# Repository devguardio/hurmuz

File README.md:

# Hürmüz - an rpi cm4 server board

Hürmüz is a devguard slice server board using the raspberry pi compute module 4 as CPU.

Ethernet is bundled via a KSZ9477 ethernet switch, where each CPU gets its own VLAN.
For recovery and management, USB is connected via an usb switch to an additional managment CPU.

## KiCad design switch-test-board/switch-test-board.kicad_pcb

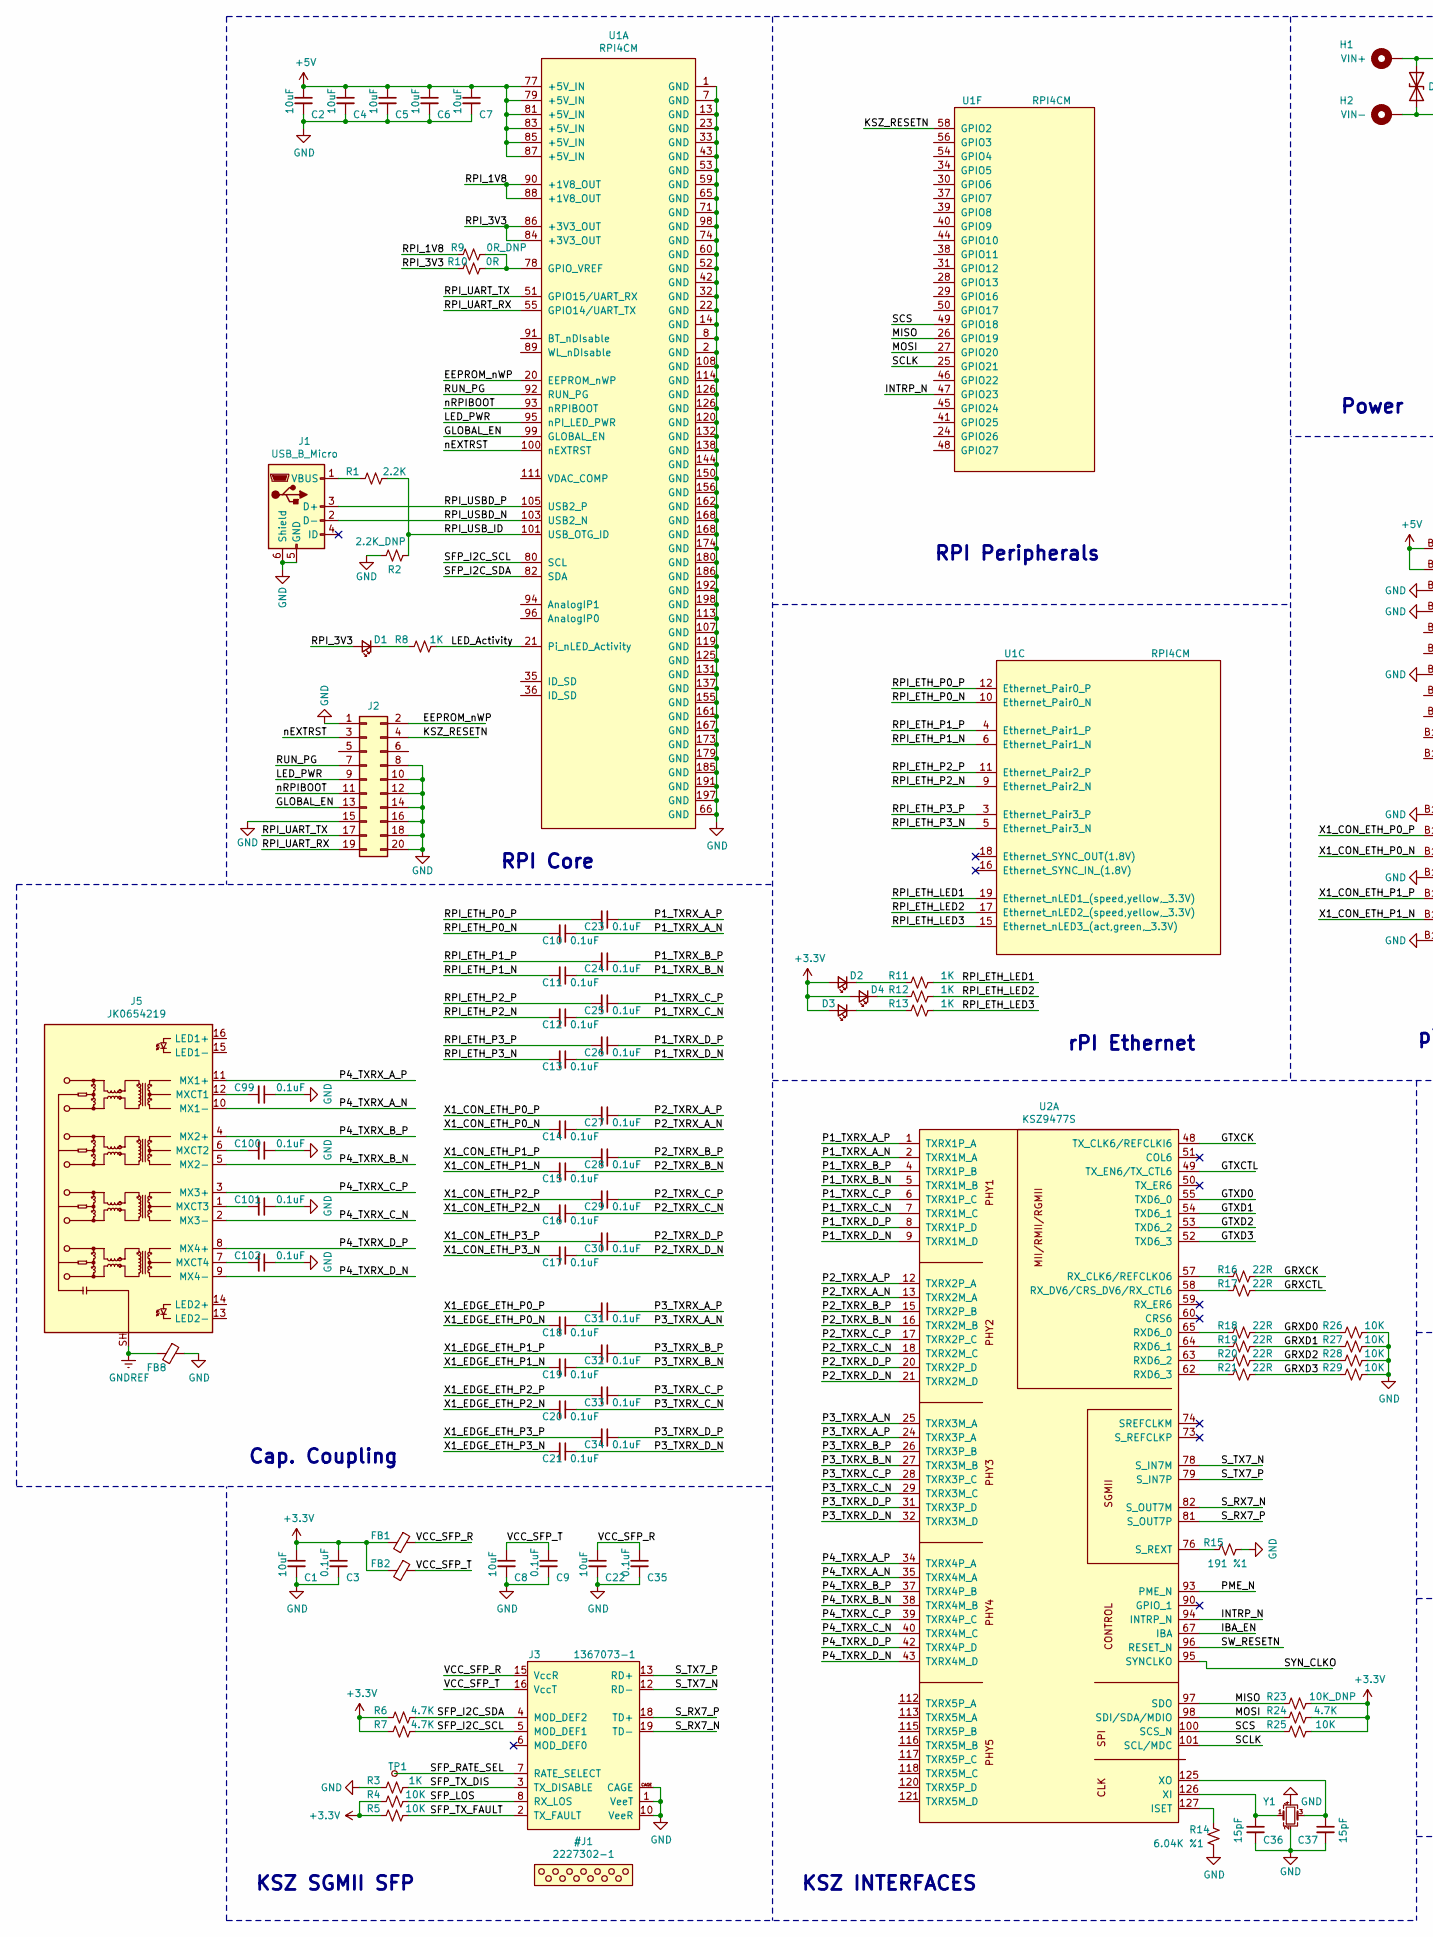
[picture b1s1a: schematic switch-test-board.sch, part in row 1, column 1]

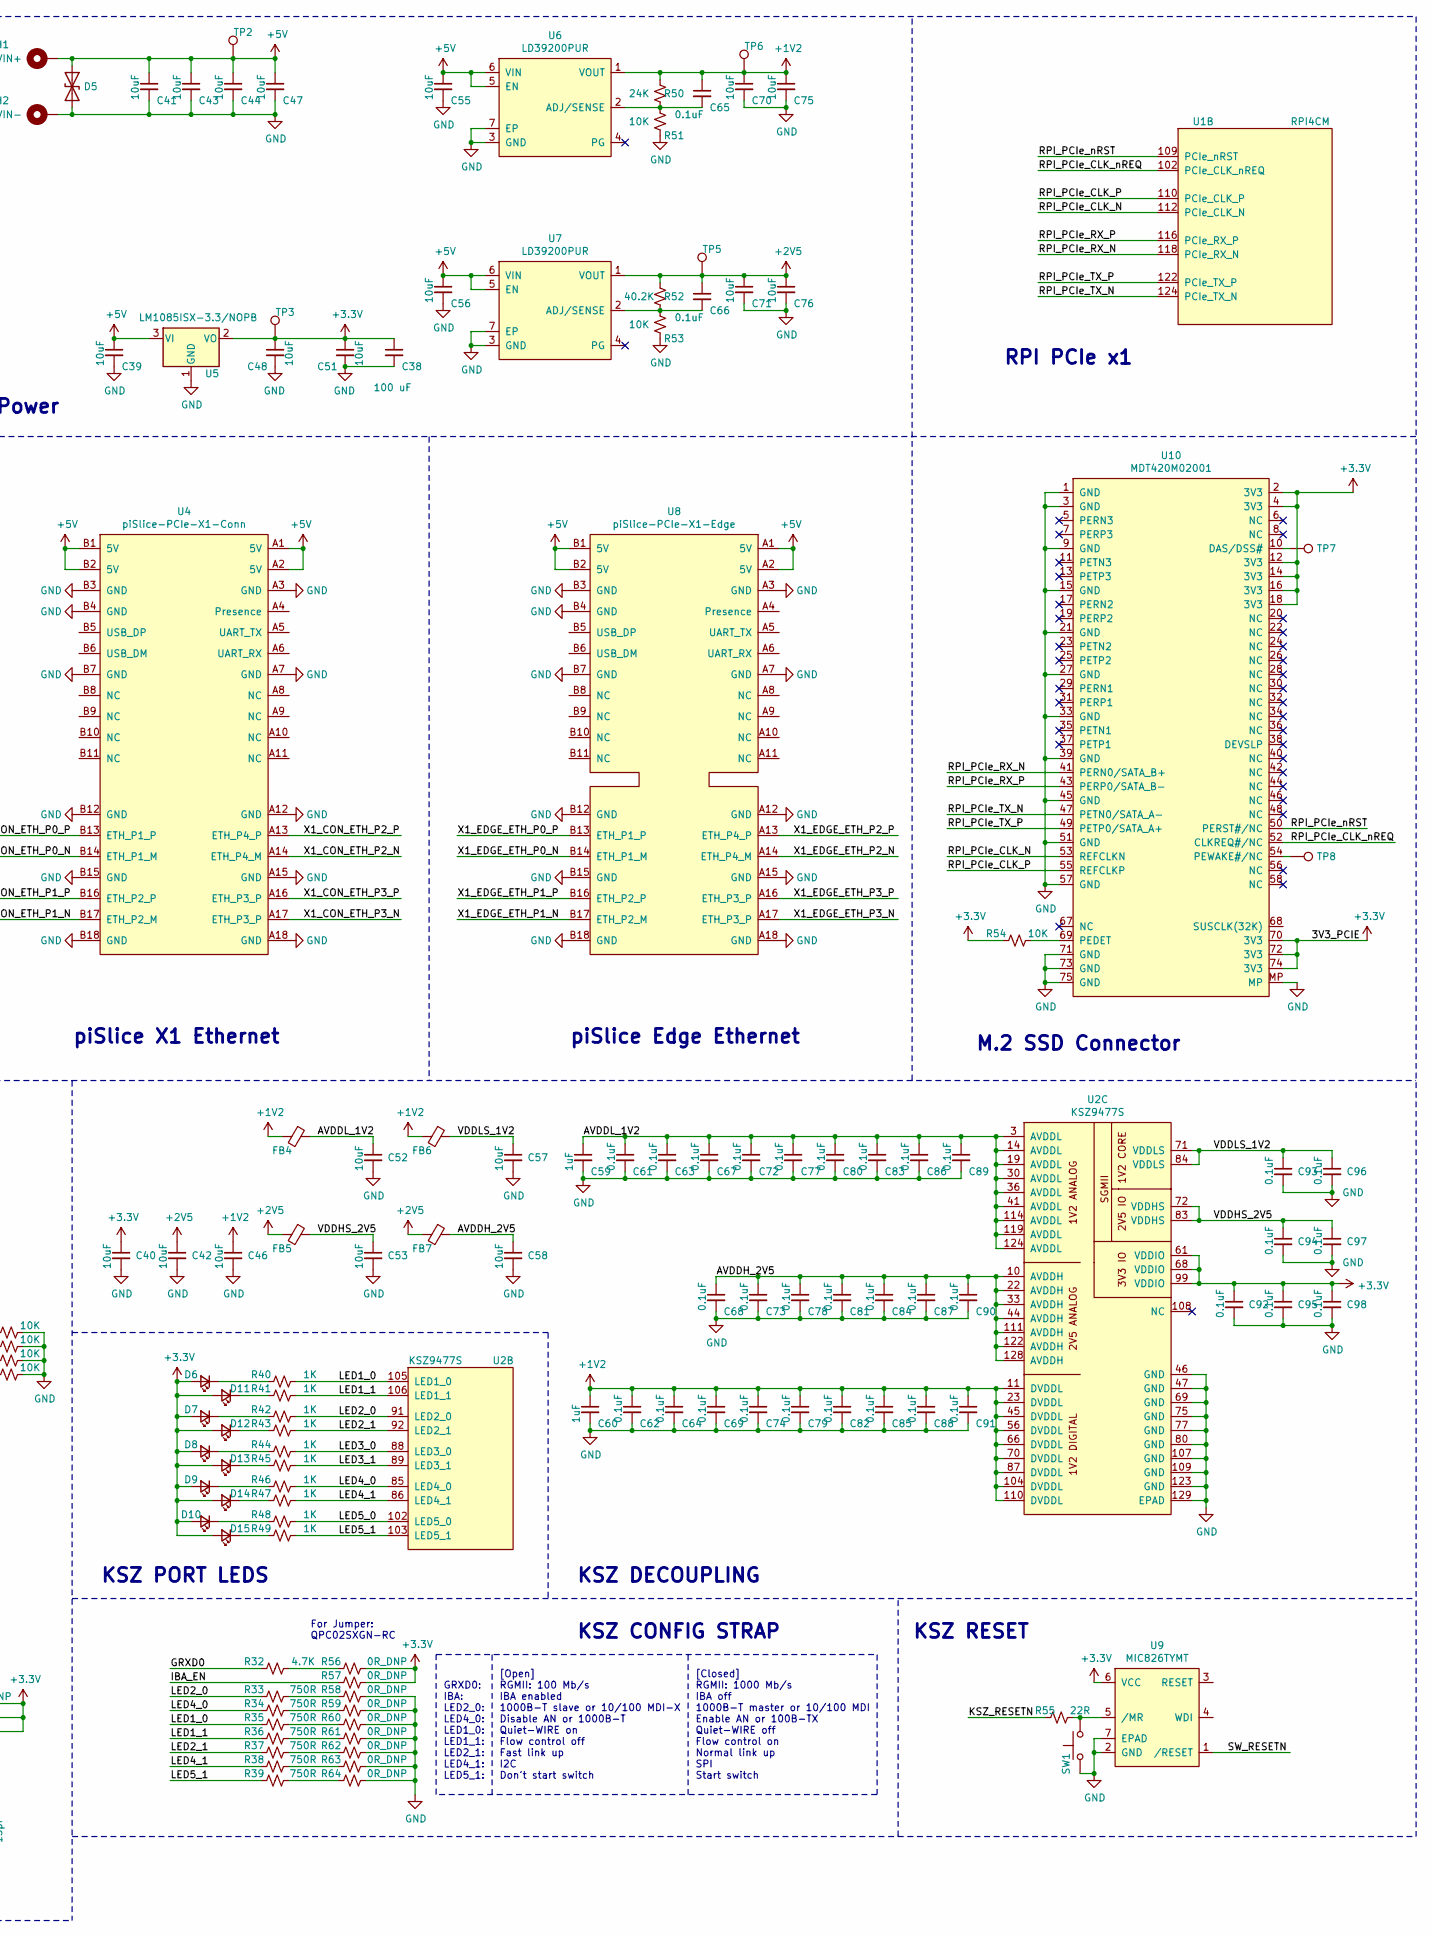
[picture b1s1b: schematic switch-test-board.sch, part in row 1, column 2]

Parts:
C1, C2, C4, C5, C6, C7, C8, C22, C39, C40, C41, C42, C43, C44, C46, C47, C48, C51, C52, C53, C55, C56, C57, C58, C70, C71, C75, C76: 10uF; C_0603_1608Metric
C3, C9, C10, C11, C12, C13, C14, C15, C16, C17, C18, C19, C20, C21, C23, C24, C25, C26, C27, C28, C29, C30, C31, C32, C33, C34, C35, C61, C62, C63, C64, C65, C66, C67, C68, C69, C72, C73, C74, C77, C78, C79, C80, C81, C82, C83, C84, C85, C86, C87, C88, C89, C90, C91, C92, C93, C94, C95, C96, C97, C98, C99, C100, C101, C102: 0.1uF; C_0402_1005Metric
C36, C37: 15pF; C_0402_1005Metric
C38: 100 uF; CP_Elec_5x5.3; Part Number 865080142007
C59, C60: 1uF; C_0402_1005Metric
D1, D2, D4, D11, D12, D13, D14, D15: 150060RS75000; LED_0603_1608Metric
D3, D6, D7, D8, D9, D10: 150060GS75000; LED_0603_1608Metric
D5: SMAJ5.0CA-TR; D_SMA
FB1, FB2, FB4, FB5, FB6, FB7, FB8: BLM18EG221SN1D; ferrite-blm18
H1: VIN+; MountingHole_3.2mm_M3_Pad
H2: VIN-; MountingHole_3.2mm_M3_Pad
J1: USB_B_Micro; USB_Micro-B_GCT_USB3076-30-A
J2: 2011-2X10G00SD025B; PinHeader_2x10_P2.54mm_Vertical
J3: 1367073-1; SFP_with_Cage
J5: JK0654219; RJ45_Pulse_JK0654219NL_Horizontal
R1: 2.2K; R_0402_1005Metric
R2: 2.2K_DNP; R_0402_1005Metric
R3, R8, R11, R12, R13, R40, R41, R42, R43, R44, R45, R46, R47, R48, R49: 1K; R_0402_1005Metric
R4, R5, R25, R26, R27, R28, R29, R51, R53, R54: 10K; R_0402_1005Metric
R6, R7, R24, R32: 4.7K; R_0402_1005Metric
R9, R56, R57, R58, R59, R60, R61, R62, R63, R64: 0R_DNP; R_0402_1005Metric
R10: 0R; R_0402_1005Metric
R14: 6.04K %1; R_0402_1005Metric
R15: 191 %1; R_0402_1005Metric
R16, R17, R18, R19, R20, R21, R55: 22R; R_0402_1005Metric
R23: 10K_DNP; R_0402_1005Metric
R33, R34, R35, R36, R37, R38, R39: 750R; R_0402_1005Metric
R50: 24K; R_0402_1005Metric
R52: 40.2K; R_0402_1005Metric
SW1: PTS645SM43SMTR92 LFS; SW_SPST_PTS645
TP1: TestPoint_Small; TestPoint_Pad_D1.0mm
TP2, TP3, TP5, TP6, TP7, TP8: TestPoint; TestPoint_Pad_D1.0mm
U1: RPI4CM; rpi-cm4
U2: KSZ9477S; 128-TQFP-EP
U4: piSlice-PCIe-X1-Conn; 10018783-10200TLF
U5: LM1085ISX-3.3/NOPB; TO-263-3_TabPin2
U6, U7: LD39200PUR; DFN-6-1EP_3x3mm_P0.95mm_EP1.7x2.6mm
U8: piSlice-PCIe-X1-Edge; piSlice_PCIexpress_x1
U9: MIC826TYMT; MLF-6-1EP_1.6x1.6mm_P0.5mm_EP0.5x1.26mm
U10: MDT420M02001; M.2_Amphenol_MDT_2280
Y1: ABM8G-25.000MHZ-B4Y-T; Crystal_SMD_Abracon_ABM8G-4Pin_3.2x2.5mm

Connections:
+1V2: C46.1, C60.1, C62.1, C64.1, C65.1, C69.1, C70.1, C74.1, C75.1, C79.1, C82.1, C85.1, C88.1, C91.1, FB4.2, FB6.2, R50.2, TP6.1, U2.11 (DVDDL), U2.23 (DVDDL), U2.45 (DVDDL), U2.56 (DVDDL), U2.66 (DVDDL), U2.70 (DVDDL), U2.87 (DVDDL), U2.104 (DVDDL), U2.110 (DVDDL), U6.1 (VOUT)
+2V5: C42.1, C66.1, C71.1, C76.1, FB5.2, FB7.2, R52.2, TP5.1, U7.1 (VOUT)
+3V3: C1.1, C3.1, C38.1, C40.1, C48.1, C51.1, C92.1, C95.1, C98.1, D2.2 (A), D3.2 (A), D4.2 (A), D6.2 (A), D7.2 (A), D8.2 (A), D9.2 (A), D10.2 (A), D11.2 (A), D12.2 (A), D13.2 (A), D14.2 (A), D15.2 (A), FB1.2, FB2.2, R4.1, R5.1, R6.1, R7.1, R23.1, R24.1, R25.1, R54.1, R56.1, R57.1, TP3.1, U2.61 (VDDIO), U2.68 (VDDIO), U2.99 (VDDIO), U5.2 (VO), U9.6 (VCC), U10.2 (3V3), U10.4 (3V3), U10.12 (3V3), U10.14 (3V3), U10.16 (3V3), U10.18 (3V3), U10.70 (3V3), U10.72 (3V3), U10.74 (3V3)
+5V: C2.1, C4.1, C5.1, C6.1, C7.1, C39.1, C41.1, C43.1, C44.1, C47.1, C55.1, C56.1, D5.1 (A1), H1.1, TP2.1, U1.77 (+5V_IN), U1.79 (+5V_IN), U1.81 (+5V_IN), U1.83 (+5V_IN), U1.85 (+5V_IN), U1.87 (+5V_IN), U4.A1 (5V), U4.A2 (5V), U4.B1 (5V), U4.B2 (5V), U5.3 (VI), U6.5 (EN), U6.6 (VIN), U7.5 (EN), U7.6 (VIN), U8.A1 (5V), U8.A2 (5V), U8.B1 (5V), U8.B2 (5V)
/AVDDH_2V5: C58.1, C68.1, C73.1, C78.1, C81.1, C84.1, C87.1, C90.1, FB7.1, U2.10 (AVDDH), U2.22 (AVDDH), U2.33 (AVDDH), U2.44 (AVDDH), U2.111 (AVDDH), U2.122 (AVDDH), U2.128 (AVDDH)
/AVDDL_1V2: C52.1, C59.1, C61.1, C63.1, C67.1, C72.1, C77.1, C80.1, C83.1, C86.1, C89.1, FB4.1, U2.3 (AVDDL), U2.14 (AVDDL), U2.19 (AVDDL), U2.30 (AVDDL), U2.36 (AVDDL), U2.41 (AVDDL), U2.114 (AVDDL), U2.119 (AVDDL), U2.124 (AVDDL)
/EEPROM_nWP: J2.2, U1.20 (EEPROM_nWP)
/GLOBAL_EN: J2.13, U1.99 (GLOBAL_EN)
/GRXCK: R16.2
/GRXCTL: R17.2
/GRXD0: R18.2, R26.1, R32.2
/GRXD1: R19.2, R27.1
/GRXD2: R20.2, R28.1
/GRXD3: R21.2, R29.1
/GTXCK: U2.48 (TX_CLK6/REFCLKI6)
/GTXCTL: U2.49 (TX_EN6/TX_CTL6)
/GTXD0: U2.55 (TXD6_0)
/GTXD1: U2.54 (TXD6_1)
/GTXD2: U2.53 (TXD6_2)
/GTXD3: U2.52 (TXD6_3)
/IBA_EN: R57.2, U2.67 (IBA)
/INTRP_N: U1.47 (GPIO23), U2.94 (INTRP_N)
/KSZ_RESETN: J2.4, R55.1, U1.58 (GPIO2)
/LED1_0: R35.2, R40.1, U2.105 (LED1_0)
/LED1_1: R36.2, R41.1, U2.106 (LED1_1)
/LED2_0: R33.2, R42.1, U2.91 (LED2_0)
/LED2_1: R37.2, R43.1, U2.92 (LED2_1)
/LED3_0: R44.1, U2.88 (LED3_0)
/LED3_1: R45.1, U2.89 (LED3_1)
/LED4_0: R34.2, R46.1, U2.85 (LED4_0)
/LED4_1: R38.2, R47.1, U2.86 (LED4_1)
/LED5_0: R48.1, U2.102 (LED5_0)
/LED5_1: R39.2, R49.1, U2.103 (LED5_1)
/LED_Activity: R8.1, U1.21 (Pi_nLED_Activity)
/LED_PWR: J2.9, U1.95 (nPI_LED_PWR)
/MISO: R23.2, U1.26 (GPIO19), U2.97 (SDO)
/MOSI: R24.2, U1.27 (GPIO20), U2.98 (SDI/SDA/MDIO)
/P1_TXRX_A_N: C10.1, U2.2 (TXRX1M_A)
/P1_TXRX_A_P: C23.1, U2.1 (TXRX1P_A)
/P1_TXRX_B_N: C11.1, U2.5 (TXRX1M_B)
/P1_TXRX_B_P: C24.1, U2.4 (TXRX1P_B)
/P1_TXRX_C_N: C12.1, U2.7 (TXRX1M_C)
/P1_TXRX_C_P: C25.1, U2.6 (TXRX1P_C)
/P1_TXRX_D_N: C13.1, U2.9 (TXRX1M_D)
/P1_TXRX_D_P: C26.1, U2.8 (TXRX1P_D)
/P2_TXRX_A_N: C14.1, U2.13 (TXRX2M_A)
/P2_TXRX_A_P: C27.1, U2.12 (TXRX2P_A)
/P2_TXRX_B_N: C15.1, U2.16 (TXRX2M_B)
/P2_TXRX_B_P: C28.1, U2.15 (TXRX2P_B)
/P2_TXRX_C_N: C16.1, U2.18 (TXRX2M_C)
/P2_TXRX_C_P: C29.1, U2.17 (TXRX2P_C)
/P2_TXRX_D_N: C17.1, U2.21 (TXRX2M_D)
/P2_TXRX_D_P: C30.1, U2.20 (TXRX2P_D)
/P3_TXRX_A_N: C18.1, U2.25 (TXRX3M_A)
/P3_TXRX_A_P: C31.1, U2.24 (TXRX3P_A)
/P3_TXRX_B_N: C19.1, U2.27 (TXRX3M_B)
/P3_TXRX_B_P: C32.1, U2.26 (TXRX3P_B)
/P3_TXRX_C_N: C20.1, U2.29 (TXRX3M_C)
/P3_TXRX_C_P: C33.1, U2.28 (TXRX3P_C)
/P3_TXRX_D_N: C21.1, U2.32 (TXRX3M_D)
/P3_TXRX_D_P: C34.1, U2.31 (TXRX3P_D)
/P4_TXRX_A_N: J5.10 (MX1-), U2.35 (TXRX4M_A)
/P4_TXRX_A_P: J5.11 (MX1+), U2.34 (TXRX4P_A)
/P4_TXRX_B_N: J5.5 (MX2-), U2.38 (TXRX4M_B)
/P4_TXRX_B_P: J5.4 (MX2+), U2.37 (TXRX4P_B)
/P4_TXRX_C_N: J5.2 (MX3-), U2.40 (TXRX4M_C)
/P4_TXRX_C_P: J5.3 (MX3+), U2.39 (TXRX4P_C)
/P4_TXRX_D_N: J5.9 (MX4-), U2.43 (TXRX4M_D)
/P4_TXRX_D_P: J5.8 (MX4+), U2.42 (TXRX4P_D)
/PME_N: U2.93 (PME_N)
/RPI_1V8: R9.1, U1.88 (+1V8_OUT), U1.90 (+1V8_OUT)
/RPI_3V3: D1.2 (A), R10.1, U1.84 (+3V3_OUT), U1.86 (+3V3_OUT)
/RPI_ETH_LED1: R11.1, U1.19 (Ethernet_nLED1_(speed,yellow,_3.3V))
/RPI_ETH_LED2: R12.1, U1.17 (Ethernet_nLED2_(speed,yellow,_3.3V))
/RPI_ETH_LED3: R13.1, U1.15 (Ethernet_nLED3_(act,green,_3.3V))
/RPI_ETH_P0_N: C10.2, U1.10 (Ethernet_Pair0_N)
/RPI_ETH_P0_P: C23.2, U1.12 (Ethernet_Pair0_P)
/RPI_ETH_P1_N: C11.2, U1.6 (Ethernet_Pair1_N)
/RPI_ETH_P1_P: C24.2, U1.4 (Ethernet_Pair1_P)
/RPI_ETH_P2_N: C12.2, U1.9 (Ethernet_Pair2_N)
/RPI_ETH_P2_P: C25.2, U1.11 (Ethernet_Pair2_P)
/RPI_ETH_P3_N: C13.2, U1.5 (Ethernet_Pair3_N)
/RPI_ETH_P3_P: C26.2, U1.3 (Ethernet_Pair3_P)
/RPI_PCIe_CLK_N: U1.112 (PCIe_CLK_N), U10.53 (REFCLKN)
/RPI_PCIe_CLK_P: U1.110 (PCIe_CLK_P), U10.55 (REFCLKP)
/RPI_PCIe_CLK_nREQ: U1.102 (PCIe_CLK_nREQ), U10.52 (CLKREQ#/NC)
/RPI_PCIe_RX_N: U1.118 (PCIe_RX_N), U10.41 (PERN0/SATA_B+)
/RPI_PCIe_RX_P: U1.116 (PCIe_RX_P), U10.43 (PERP0/SATA_B-)
/RPI_PCIe_TX_N: U1.124 (PCIe_TX_N), U10.47 (PETN0/SATA_A-)
/RPI_PCIe_TX_P: U1.122 (PCIe_TX_P), U10.49 (PETP0/SATA_A+)
/RPI_PCIe_nRST: U1.109 (PCIe_nRST), U10.50 (PERST#/NC)
/RPI_UART_RX: J2.19, U1.55 (GPIO14/UART_TX)
/RPI_UART_TX: J2.17, U1.51 (GPIO15/UART_RX)
/RPI_USBD_N: J1.2 (D-), U1.103 (USB2_N)
/RPI_USBD_P: J1.3 (D+), U1.105 (USB2_P)
/RPI_USB_ID: R1.1, R2.2, U1.101 (USB_OTG_ID)
/RUN_PG: J2.7, U1.92 (RUN_PG)
/SCLK: U1.25 (GPIO21), U2.101 (SCL/MDC)
/SCS: R25.2, U1.49 (GPIO18), U2.100 (SCS_N)
/SFP_I2C_SCL: J3.5 (MOD_DEF1), R7.2, U1.80 (SCL)
/SFP_I2C_SDA: J3.4 (MOD_DEF2), R6.2, U1.82 (SDA)
/SFP_LOS: J3.8 (RX_LOS), R4.2
/SFP_RATE_SEL: J3.7 (RATE_SELECT), TP1.1
/SFP_TX_DIS: J3.3 (TX_DISABLE), R3.2
/SFP_TX_FAULT: J3.2 (TX_FAULT), R5.2
/SW_RESETN: U2.96 (RESET_N), U9.1 (/RESET)
/SYN_CLKO: U2.95 (SYNCLKO)
/S_RX7_N: J3.19 (TD-), U2.82 (S_OUT7M)
/S_RX7_P: J3.18 (TD+), U2.81 (S_OUT7P)
/S_TX7_N: J3.12 (RD-), U2.78 (S_IN7M)
/S_TX7_P: J3.13 (RD+), U2.79 (S_IN7P)
/VCC_SFP_R: C22.1, C35.1, FB1.1, J3.15 (VccR)
/VCC_SFP_T: C8.1, C9.1, FB2.1, J3.16 (VccT)
/VDDHS_2V5: C53.1, C94.1, C97.1, FB5.1, U2.72 (VDDHS), U2.83 (VDDHS)
/VDDLS_1V2: C57.1, C93.1, C96.1, FB6.1, U2.71 (VDDLS), U2.84 (VDDLS)
/X1_CON_ETH_P0_N: C14.2, U4.B14 (ETH_P1_M)
/X1_CON_ETH_P0_P: C27.2, U4.B13 (ETH_P1_P)
/X1_CON_ETH_P1_N: C15.2, U4.B17 (ETH_P2_M)
/X1_CON_ETH_P1_P: C28.2, U4.B16 (ETH_P2_P)
/X1_CON_ETH_P2_N: C16.2, U4.A14 (ETH_P4_M)
/X1_CON_ETH_P2_P: C29.2, U4.A13 (ETH_P4_P)
/X1_CON_ETH_P3_N: C17.2, U4.A17 (ETH_P3_P)
/X1_CON_ETH_P3_P: C30.2, U4.A16 (ETH_P3_P)
/X1_EDGE_ETH_P0_N: C18.2, U8.B14 (ETH_P1_M)
/X1_EDGE_ETH_P0_P: C31.2, U8.B13 (ETH_P1_P)
/X1_EDGE_ETH_P1_N: C19.2, U8.B17 (ETH_P2_M)
/X1_EDGE_ETH_P1_P: C32.2, U8.B16 (ETH_P2_P)
/X1_EDGE_ETH_P2_N: C20.2, U8.A14 (ETH_P4_M)
/X1_EDGE_ETH_P2_P: C33.2, U8.A13 (ETH_P4_P)
/X1_EDGE_ETH_P3_N: C21.2, U8.A17 (ETH_P3_P)
/X1_EDGE_ETH_P3_P: C34.2, U8.A16 (ETH_P3_P)
/nEXTRST: J2.3, U1.100 (nEXTRST)
/nRPIBOOT: J2.11, U1.93 (nRPIBOOT)
GND: C1.2, C2.2, C3.2, C4.2, C5.2, C6.2, C7.2, C8.2, C9.2, C22.2, C35.2, C36.2, C37.2, C38.2, C39.2, C40.2, C41.2, C42.2, C43.2, C44.2, C46.2, C47.2, C48.2, C51.2, C52.2, C53.2, C55.2, C56.2, C57.2, C58.2, C59.2, C60.2, C61.2, C62.2, C63.2, C64.2, C67.2, C68.2, C69.2, C70.2, C71.2, C72.2, C73.2, C74.2, C75.2, C76.2, C77.2, C78.2, C79.2, C80.2, C81.2, C82.2, C83.2, C84.2, C85.2, C86.2, C87.2, C88.2, C89.2, C90.2, C91.2, C92.2, C93.2, C94.2, C95.2, C96.2, C97.2, C98.2, C99.1, C100.1, C101.1, C102.1, D5.2 (A2), FB8.1, H2.1, J1.5 (GND), J1.6 (Shield), J2.1, J2.8, J2.10, J2.12, J2.14, J2.15, J2.16, J2.18, J2.20, J3.1 (VeeT), J3.9 (VeeR), J3.10 (VeeR), J3.11 (VeeR), J3.14 (VeeR), J3.17 (VeeT), J3.20 (VeeT), J3.CAGE, R2.1, R3.1, R14.1, R15.2, R26.2, R27.2, R28.2, R29.2, R51.1, R53.1, R58.1, R59.1, R60.1, R61.1, R62.1, R63.1, R64.1, SW1.1, U1.1 (GND), U1.2 (GND), U1.7 (GND), U1.8 (GND), U1.13 (GND), U1.14 (GND), U1.22 (GND), U1.23 (GND), U1.32 (GND), U1.33 (GND), U1.42 (GND), U1.43 (GND), U1.52 (GND), U1.53 (GND), U1.59 (GND), U1.60 (GND), U1.65 (GND), U1.66 (GND), U1.71 (GND), U1.74 (GND), U1.98 (GND), U1.107 (GND), U1.108 (GND), U1.113 (GND), U1.114 (GND), U1.119 (GND), U1.120 (GND), U1.125 (GND), U1.126 (GND), U1.131 (GND), U1.132 (GND), U1.137 (GND), U1.138 (GND), U1.144 (GND), U1.150 (GND), U1.155 (GND), U1.156 (GND), U1.161 (GND), U1.162 (GND), U1.167 (GND), U1.168 (GND), U1.173 (GND), U1.174 (GND), U1.179 (GND), U1.180 (GND), U1.185 (GND), U1.186 (GND), U1.191 (GND), U1.192 (GND), U1.197 (GND), U1.198 (GND), U2.46 (GND), U2.47 (GND), U2.69 (GND), U2.75 (GND), U2.77 (GND), U2.80 (GND), U2.107 (GND), U2.109 (GND), U2.123 (GND), U2.129 (EPAD), U4.A3 (GND), U4.A7 (GND), U4.A12 (GND), U4.A15 (GND), U4.A18 (GND), U4.B3 (GND), U4.B4 (GND), U4.B7 (GND), U4.B12 (GND), U4.B15 (GND), U4.B18 (GND), U5.1 (GND), U6.3 (GND), U6.7 (EP), U7.3 (GND), U7.7 (EP), U8.A3 (GND), U8.A7 (GND), U8.A12 (GND), U8.A15 (GND), U8.A18 (GND), U8.B3 (GND), U8.B4 (GND), U8.B7 (GND), U8.B12 (GND), U8.B15 (GND), U8.B18 (GND), U9.2 (GND), U9.7 (EPAD), U10.1 (GND), U10.3 (GND), U10.9 (GND), U10.15 (GND), U10.21 (GND), U10.27 (GND), U10.33 (GND), U10.39 (GND), U10.45 (GND), U10.51 (GND), U10.57 (GND), U10.71 (GND), U10.73 (GND), U10.75 (GND), U10.MP, Y1.2, Y1.4
GNDREF: FB8.2, J5.SH
unnamed: C36.1, U2.126 (XI), Y1.1
unnamed: C37.1, U2.125 (XO), Y1.3
unnamed: C65.2, R50.1, R51.2, U6.2 (ADJ/SENSE)
unnamed: C66.2, R52.1, R53.2, U7.2 (ADJ/SENSE)
unnamed: C99.2, J5.12 (MXCT1)
unnamed: C100.2, J5.6 (MXCT2)
unnamed: C101.2, J5.1 (MXCT3)
unnamed: C102.2, J5.7 (MXCT4)
unnamed: D1.1 (K), R8.2
unnamed: D2.1 (K), R11.2
unnamed: D3.1 (K), R13.2
unnamed: D4.1 (K), R12.2
unnamed: D6.1 (K), R40.2
unnamed: D7.1 (K), R42.2
unnamed: D8.1 (K), R44.2
unnamed: D9.1 (K), R46.2
unnamed: D10.1 (K), R48.2
unnamed: D11.1 (K), R41.2
unnamed: D12.1 (K), R43.2
unnamed: D13.1 (K), R45.2
unnamed: D14.1 (K), R47.2
unnamed: D15.1 (K), R49.2
unnamed: J1.1 (VBUS), R1.2
unnamed: R9.2, R10.2, U1.78 (GPIO_VREF)
unnamed: R14.2, U2.127 (ISET)
unnamed: R15.1, U2.76 (S_REXT)
unnamed: R16.1, U2.57 (RX_CLK6/REFCLKO6)
unnamed: R17.1, U2.58 (RX_DV6/CRS_DV6/RX_CTL6)
unnamed: R18.1, U2.65 (RXD6_0)
unnamed: R19.1, U2.64 (RXD6_1)
unnamed: R20.1, U2.63 (RXD6_2)
unnamed: R21.1, U2.62 (RXD6_3)
unnamed: R32.1, R56.2
unnamed: R33.1, R58.2
unnamed: R34.1, R59.2
unnamed: R35.1, R60.2
unnamed: R36.1, R61.2
unnamed: R37.1, R62.2
unnamed: R38.1, R63.2
unnamed: R39.1, R64.2
unnamed: R54.2, U10.69 (PEDET)
unnamed: R55.2, SW1.2, U9.5 (/MR)
unnamed: TP7.1, U10.10 (DAS/DSS#)
unnamed: TP8.1, U10.54 (PEWAKE#/NC)

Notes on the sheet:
For Jumper: QPC02SXGN-RC
GRXD0: IBA: LED2_0: LED4_0: LED1_0: LED1_1: LED2_1: LED4_1: LED5_1:
[Closed] RGMII: 1000 Mb/s IBA off 1000B-T master or 10/100 MDI Enable AN or 100B-TX Quiet-WIRE off Flow control on Normal link up SPI Start switch
[Open] RGMII: 100 Mb/s IBA enabled 1000B-T slave or 10/100 MDI-X Disable AN or 1000B-T Quiet-WIRE on Flow control off Fast link up I2C Don't start switch
KSZ CONFIG STRAP
KSZ RESET
KSZ DECOUPLING
KSZ PORT LEDS
KSZ INTERFACES
KSZ SGMII SFP
M.2 SSD Connector
piSlice Edge Ethernet
piSlice X1 Ethernet
Power
RPI PCIe x1
Cap. Coupling
rPI Ethernet
RPI Peripherals
RPI Core

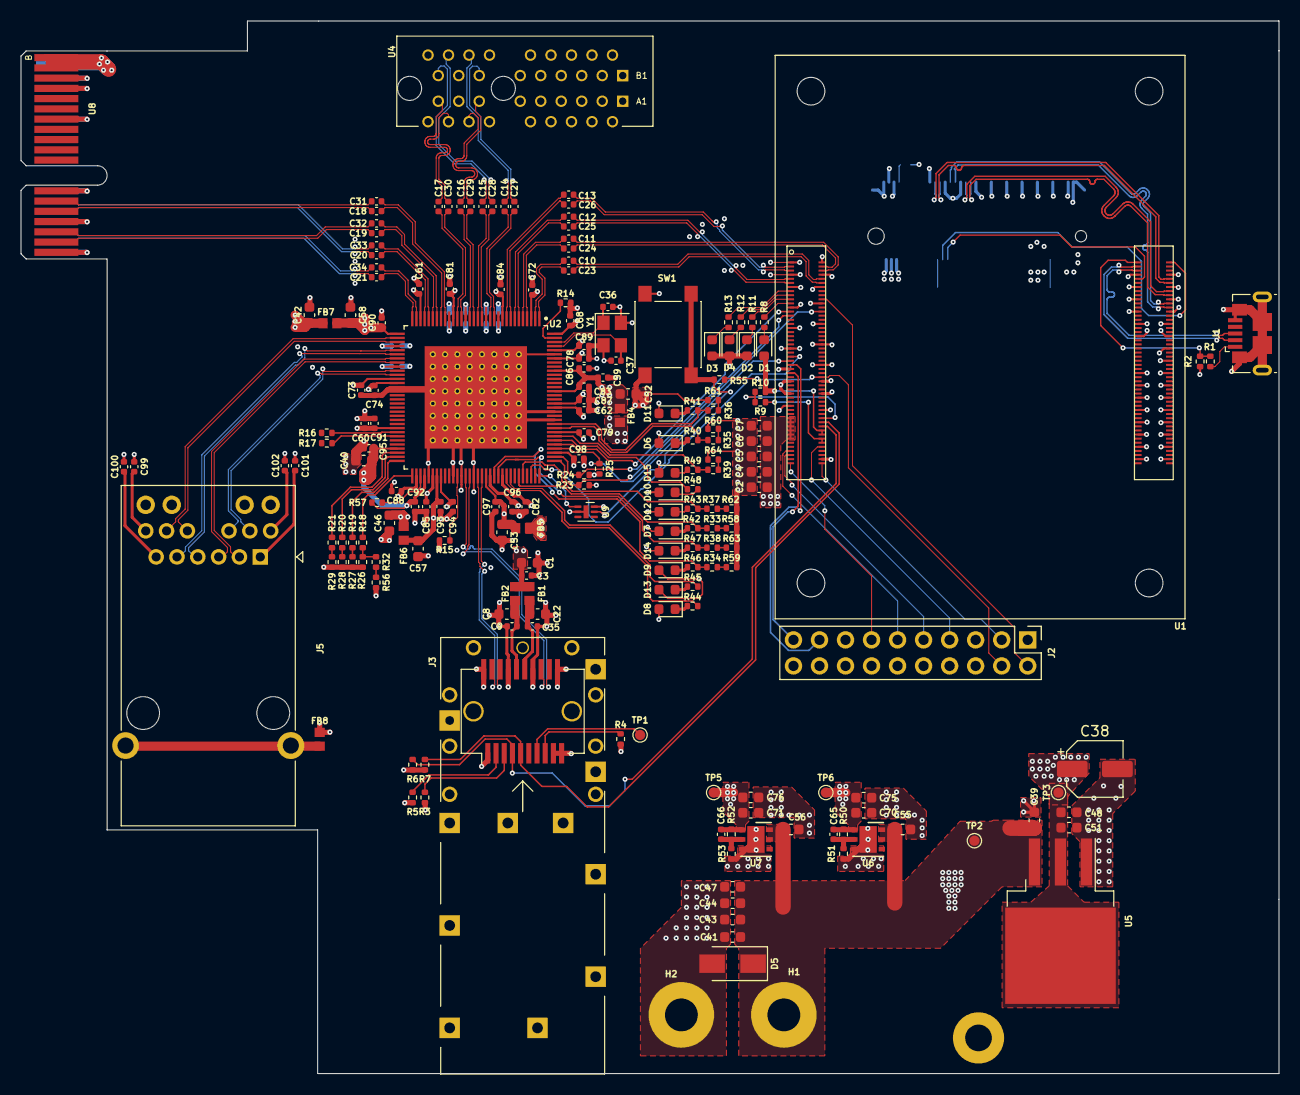
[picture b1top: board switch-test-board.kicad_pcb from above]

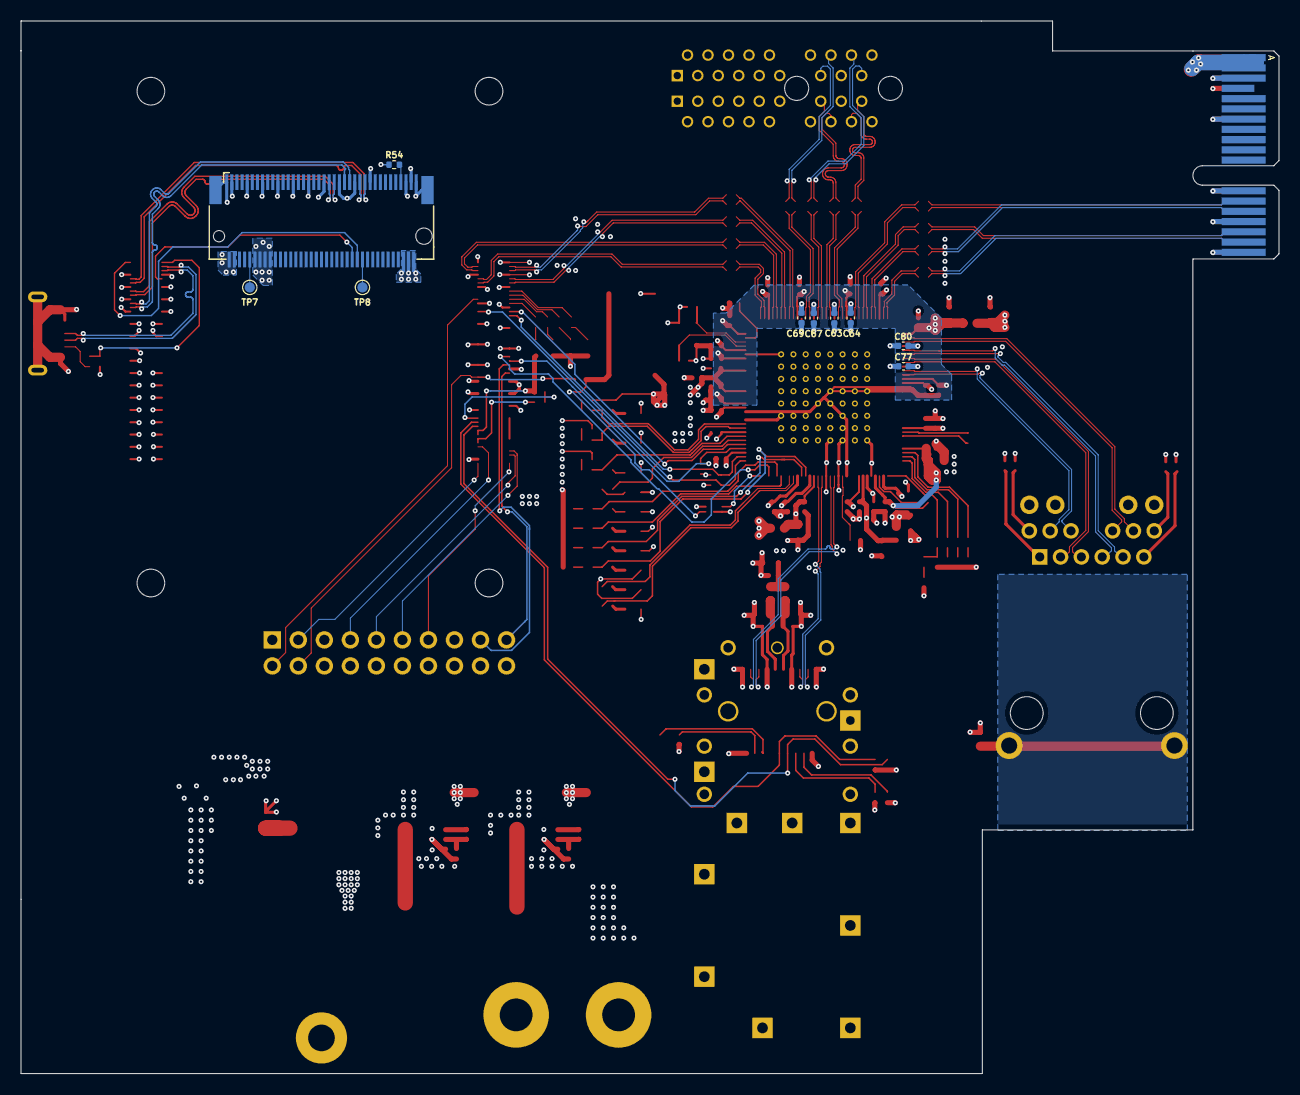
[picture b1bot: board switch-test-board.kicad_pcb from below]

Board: 4 copper layers, 122.8 x 102.7 mm, 205 parts (10 on the bottom side), 169 nets.

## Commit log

2021-03-24 Updated Sch.
2021-03-24 Sch. update.
2021-03-24 Added KSZ Switch IC Decoupling and Port Leds.
2021-03-28 Updated Schematic.
2021-03-28 Added PCIe x1 to NVMe adapter.
2021-03-29 Schematic completed.
2021-03-30 PCB Design planning.
2021-03-31 Create LICENSE
2021-04-04 PCB Design Updated.
2021-04-04 Completed routing eth. interfaces.
2021-04-25 PCB updated.
2021-05-19 PCB Design Completed.
